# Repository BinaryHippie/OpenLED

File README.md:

# OpenLED

OpenLED is a low-profile addressable RGB LED board intended for mounting on
OpenDrone frame arms. Each board carries four individually addressable
WS2812B-V6 LEDs and connects using solder pads for 5 V, ground and LED data.
An output set provides 5 V, ground and DOUT for optional daisy chaining.

The current design is a fixed 37 x 7 mm rigid PCB. It does not carry motor
current and does not include an onboard controller; LED data and 5 V power are
provided by the flight controller or another compatible source.

## Why

Arm-mounted LEDs can provide orientation, status indication and visual effects
without requiring a separate bulky lighting module.

OpenLED keeps the board simple: four addressable LEDs, direct solder-pad
connections and no additional controller. The design is intended to remain
lightweight, low profile, repairable and easy to integrate with OpenDrone
hardware.

The first revision is being developed as a reusable arm LED board. Prototype
PCBs are currently generated as 1x4 manufacturing panels and hand assembled.
Mechanical fit on the intended OpenFrame sizes must be verified physically
before frame compatibility is treated as final.

## Specifications

| | |
|---|---|
| Supply voltage | 5 V |
| LEDs | 4x WS2812B-V6 |
| LED type | Individually addressable RGB |
| Data interface | DIN / DOUT |
| Input connections | 5 V, GND, DIN solder pads |
| Output connections | 5 V, GND, DOUT solder pads |
| Bulk capacitance | 2x 10 uF |
| Local decoupling | 4x 100 nF, one per LED |
| PCB size | 37 x 7 mm |
| PCB thickness | 0.8 mm |
| Copper layers | 2 |
| Copper weight | 35 um |
| Board material | FR4 |

## Constraints

- The board is powered from a regulated 5 V source.
- Motor current must not be routed through the OpenLED PCB.
- The board has no onboard MCU or LED protocol controller.
- LED data enters at DIN and propagates through D1-D4 to DOUT.
- Each LED has a dedicated 100 nF local decoupling capacitor.
- Connections use solder pads rather than board-mounted connectors to minimise
  height and weight.
- The PCB is 37 x 7 mm with 1 mm corner radii.
- The design uses a front-layer 5 V plane and a back-layer GND plane.
- The board is intended for arm mounting and should remain compatible with
  heat-shrink or another lightweight strain-relief method.
- Mechanical compatibility with each intended OpenFrame size must be physically
  verified before release.
- Components should retain exact Manufacturer, MPN and LCSC fields where
  applicable.
- The project is authored in KiCad 10.
- Prototype panel generation is documented in `hardware/PANELIZATION.md`; the
  standalone `hardware/OpenLED.kicad_pcb` remains the board design source of
  truth.

## Design questions

- Confirm physical fit and mounting method on each intended OpenFrame size.
- Confirm the preferred wire routing and strain-relief method on an assembled
  arm.
- Validate LED visibility and spacing when installed under the intended
  protective covering.
- Confirm the production PCB finish and final assembly process after prototype
  testing.

## In the line

OpenLED is intended as an optional lighting accessory for OpenDrone builds.

It is designed to accept a 5 V supply and an addressable LED data signal from a
compatible flight controller, while retaining DOUT for optional chaining.

What pairs with what, and what is available:
[opendrone.be](https://opendrone.be).

## Contributing

See [CONTRIBUTING.md](CONTRIBUTING.md).

## License

Hardware licensed under
[CERN-OHL-S-2.0](https://ohwr.org/cern_ohl_s_v2.txt), see [LICENSE](LICENSE).

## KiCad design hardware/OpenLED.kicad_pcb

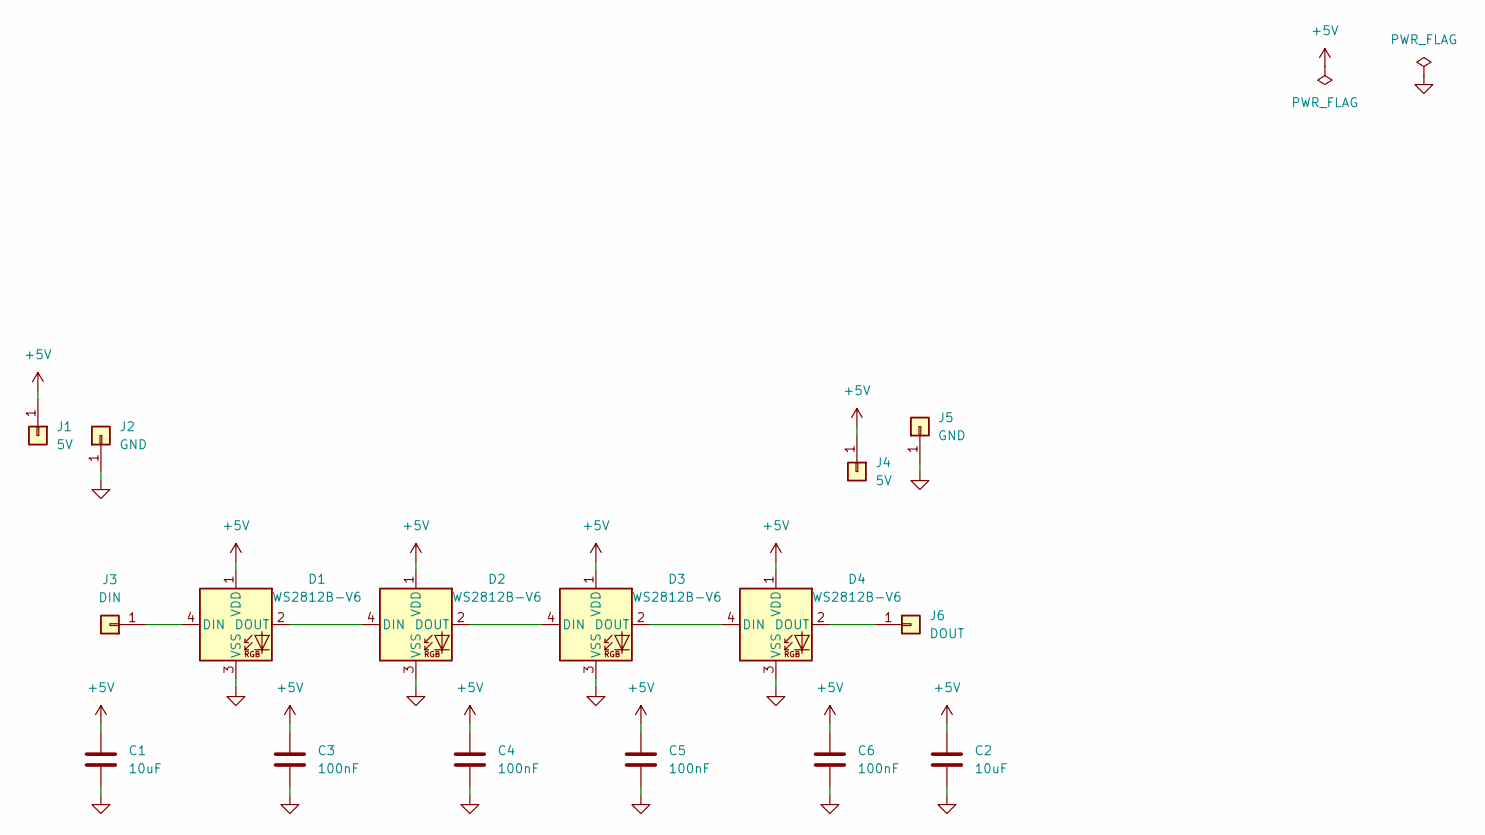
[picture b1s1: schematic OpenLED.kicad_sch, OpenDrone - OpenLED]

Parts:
C1, C2: 10uF; C_0603_1608Metric; MPN CL10A106KO8NQNC; LCSC C962136
C3, C4, C5, C6: 100nF; C_0402_1005Metric; MPN CL05B104KO5NNNC; LCSC C1525
D1, D2, D3, D4: WS2812B-V6; LED_WS2812B_PLCC4_5.0x5.0mm_P3.2mm; MPN WS2812B-V6; LCSC C52917433
J1, J4: 5V; SolderPad_2.2x1.6mm
J2, J5: GND; SolderPad_2.2x1.6mm
J3: DIN; SolderPad_2.2x1.6mm
J6: DOUT; SolderPad_2.2x1.6mm

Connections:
+5V: C1.1, C2.1, C3.1, C4.1, C5.1, C6.1, D1.1 (VDD), D2.1 (VDD), D3.1 (VDD), D4.1 (VDD), J1.1 (Pin_1_1), J4.1 (Pin_1_1)
GND: C1.2, C2.2, C3.2, C4.2, C5.2, C6.2, D1.3 (VSS), D2.3 (VSS), D3.3 (VSS), D4.3 (VSS), J2.1 (Pin_1_1), J5.1 (Pin_1_1)
unnamed: D1.4 (DIN), J3.1 (Pin_1_1)
unnamed: D1.2 (DOUT), D2.4 (DIN)
unnamed: D2.2 (DOUT), D3.4 (DIN)
unnamed: D3.2 (DOUT), D4.4 (DIN)
unnamed: D4.2 (DOUT), J6.1 (Pin_1_1)

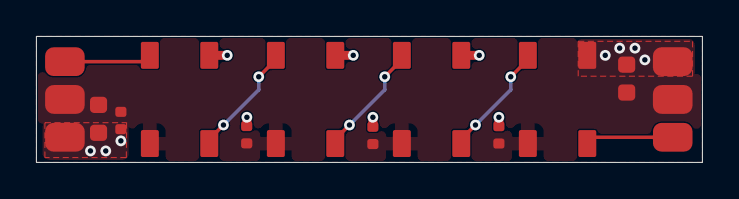
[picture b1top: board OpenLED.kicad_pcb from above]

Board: 2 copper layers, 37.0 x 7.0 mm, 16 parts (0 on the bottom side), 7 nets.
